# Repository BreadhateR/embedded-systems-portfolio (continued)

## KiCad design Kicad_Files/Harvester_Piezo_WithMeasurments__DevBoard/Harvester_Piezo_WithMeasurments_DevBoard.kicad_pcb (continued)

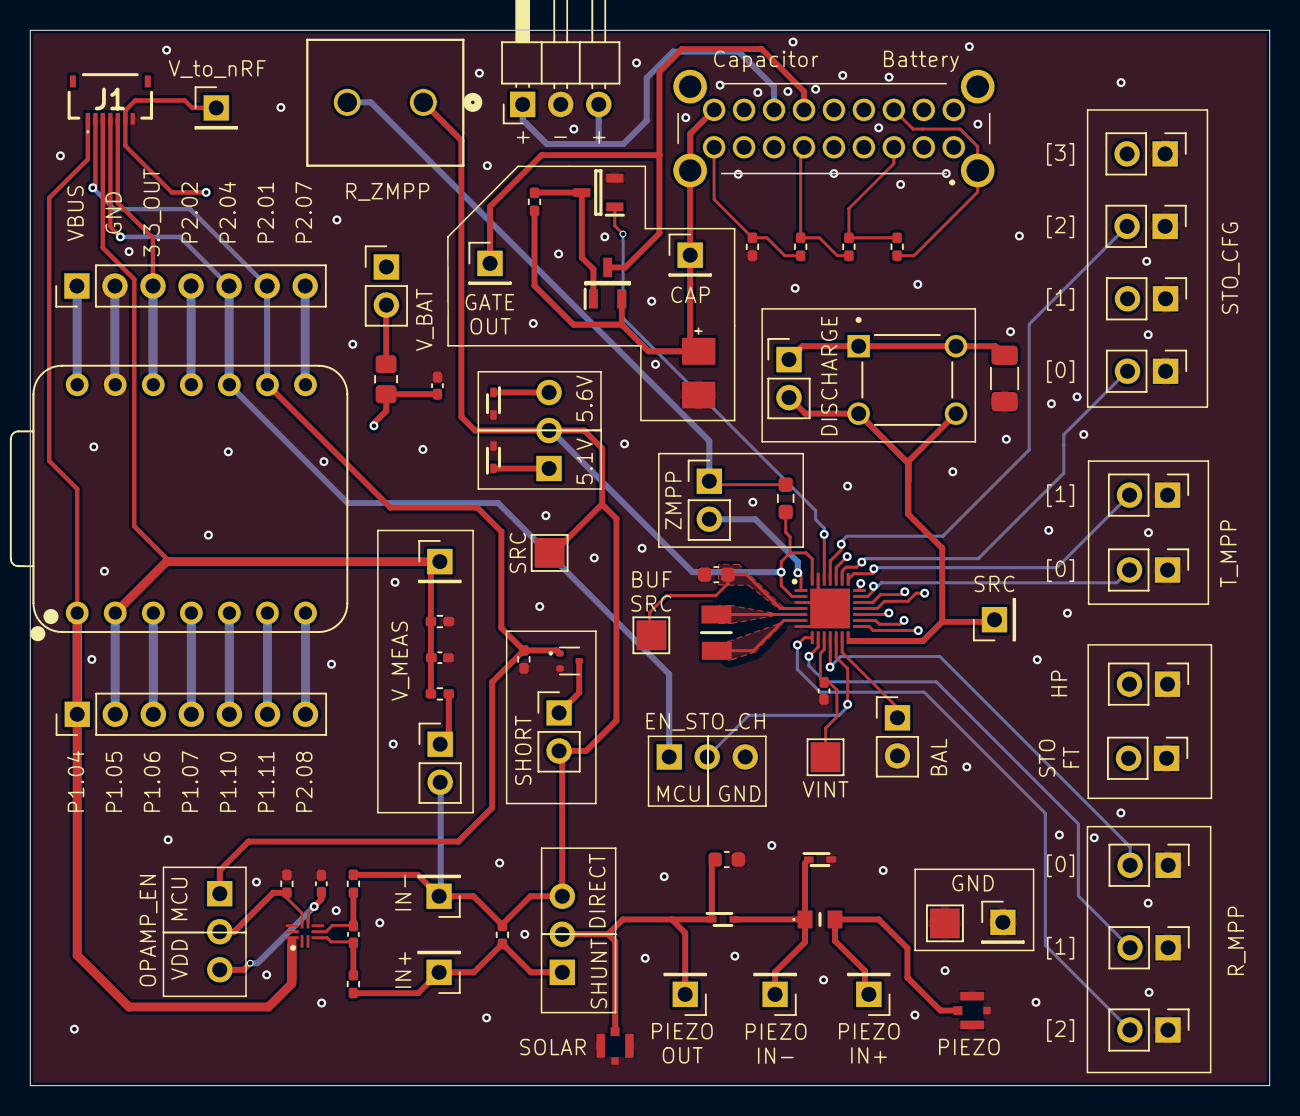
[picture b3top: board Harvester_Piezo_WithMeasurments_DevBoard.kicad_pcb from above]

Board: 4 copper layers, 82.7 x 70.5 mm, 80 parts (0 on the bottom side), 61 nets.

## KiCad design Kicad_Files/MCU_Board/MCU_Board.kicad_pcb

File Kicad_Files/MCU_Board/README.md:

# Nordic nRF54L Custom Development Board

Custom Nordic MCU development-board design for firmware prototyping, peripheral access, and debugging. The supplied schematic and PCB specify **`NRF54L15-QFAA-R`**; 

Development covered the MCU support circuit, supply filtering and decoupling, clock components, RF network, schematic capture, and PCB layout. This is a separate board design; it is not the existing flexible SiSmaK electronics.

## Hardware Features

- **Microcontroller:** Nordic nRF54L15 in the supplied Value/MPN fields
- **RF Circuit:** Discrete matching network and ACAG0201-2450-T chip antenna
- **Clocking:** External high-frequency crystal oscillator
- **Power Supply:** Direct external supply with MCU decoupling and filtering
- **Debugging:** SWD interface for programming and debugging
- **GPIO Expansion:** Pin headers providing access to MCU GPIOs and peripheral interfaces
- **User Interface:** Reset button, user button, and two status LEDs

### Debugging and Peripheral Access

SWDIO, SWDCLK, and reset connections provide programming/debug access. Pin headers expose GPIOs, including signals labelled for peripheral buses, so external circuits can be connected without modifying the PCB.

Two LEDs, a user button, and a reset button provide local controls and status outputs. These are hardware provisions; tested firmware drivers and peripheral functionality are not documented for this board.

## PCB Design

The four-layer PCB was designed using **KiCad 9**. The project includes custom design rules alongside the schematic and layout.

### PCB Layout

## Schematics

The existing hardware PDF export is available here:

[View Schematic (PDF)](Hardware_Design.pdf)

The original KiCad project files are also included for further inspection.

## Design Files

| File | Description |
|---|---|
| [`MCU_Board.kicad_pro`](MCU_Board.kicad_pro) | KiCad project |
| [`MCU_Board.kicad_sch`](MCU_Board.kicad_sch) | Main schematic |
| [`MCU.kicad_sch`](MCU.kicad_sch) | MCU schematic sheet |
| [`MCU_Board.kicad_pcb`](MCU_Board.kicad_pcb) | PCB layout |
| [`MCU_Board.kicad_dru`](MCU_Board.kicad_dru) | Custom design rules |

---

**Author:** Alexander Richter  
**Institution:** TU Darmstadt

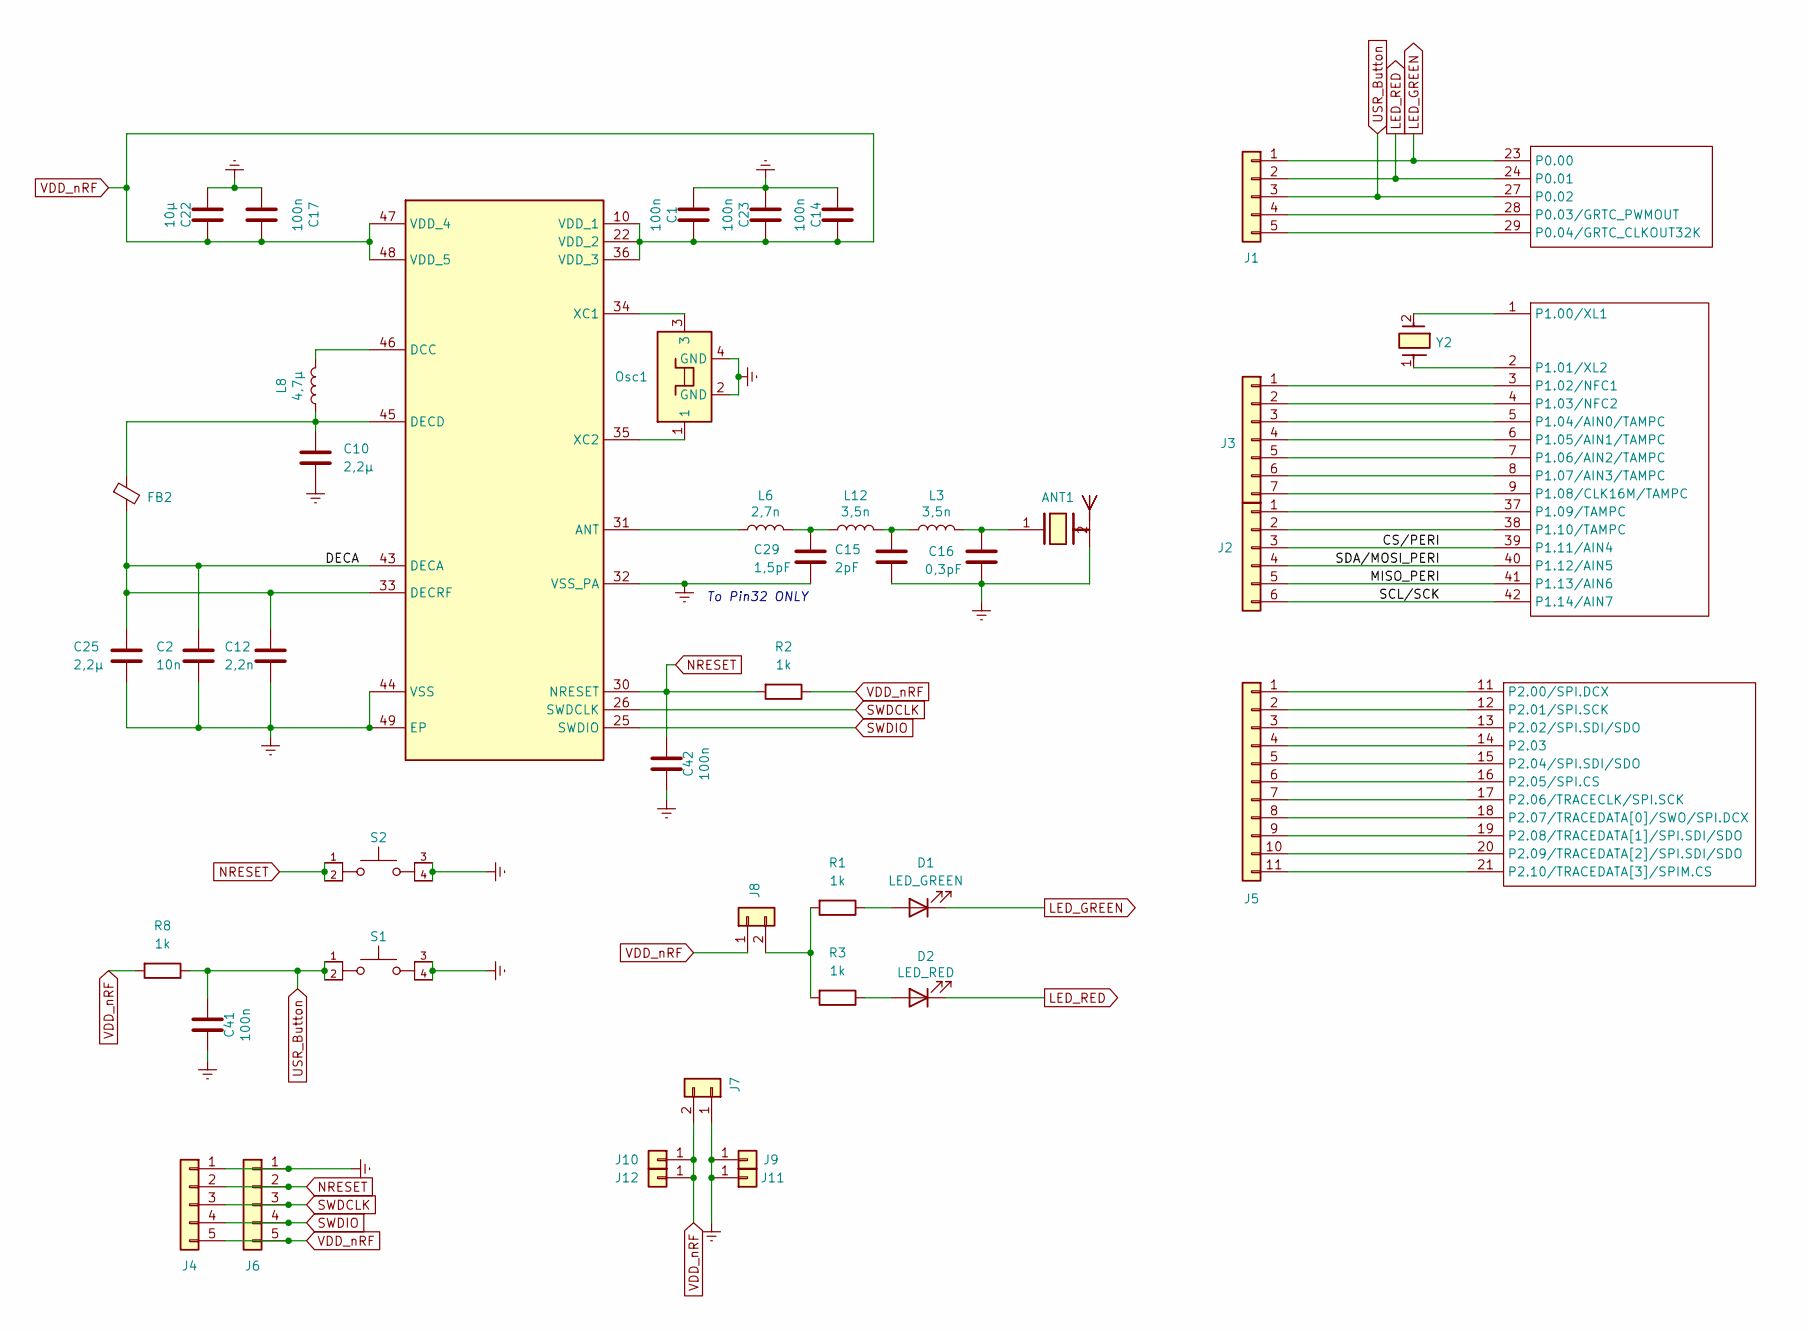
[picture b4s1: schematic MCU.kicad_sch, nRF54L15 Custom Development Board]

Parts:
ANT1: ACAG0201-2450-T; ANTC2012X70N; Manufacturer_Part_Number ACAG0201-2450-T; Mouser Part Number 815-G0201-2450-T
C1, C14, C17, C23, C41, C42: 100n; C_0603_1608Metric_Pad1.08x0.95mm_HandSolder; MPN CC0603KRX7R7BB104
C2: 10n; C_0603_1608Metric_Pad1.08x0.95mm_HandSolder; MPN C0603C103K9RACTU
C10, C25: 2,2µ; C_0603_1608Metric_Pad1.08x0.95mm_HandSolder; MPN CGA3E1X7R0J225K080AC
C12: 2,2n; C_0603_1608Metric_Pad1.08x0.95mm_HandSolder; MPN CC0603KRX7R7BB222
C15: 2pF; C_0603_1608Metric_Pad1.08x0.95mm_HandSolder; MPN RF18N2R0A500CT
C16: 0,3pF; C_0603_1608Metric_Pad1.08x0.95mm_HandSolder; MPN RF18N0R3B500CT
C22: 10µ; C_0603_1608Metric_Pad1.08x0.95mm_HandSolder; MPN CL10A106KQ8NNNC
C29: 1,5pF; C_0603_1608Metric_Pad1.08x0.95mm_HandSolder; MPN RF18N1R5A500CT
D1: LED_GREEN; LED_0603_1608Metric_Pad1.05x0.95mm_HandSolder; MPN APT1608CGCK
D2: LED_RED; LED_0603_1608Metric_Pad1.05x0.95mm_HandSolder; MPN VFHR1111C-3BY2A-TR
FB2: FerriteBead_Small; L_0603_1608Metric_Pad1.05x0.95mm_HandSolder; MPN 2506031217H0
IC1: NRF54L10-QFAA-R; QFN40P600X600X90-49N; Mouser Part Number 949-NRF54L10-QFAA-R
J1, J6: Conn_01x05; PinHeader_1x05_P2.54mm_Vertical
J2: Conn_01x06; PinHeader_1x06_P2.54mm_Vertical
J3: Conn_01x07; PinHeader_1x07_P2.54mm_Vertical
J4: Conn_01x05; JST_XH_B5B-XH-A_1x05_P2.50mm_Vertical
J5: Conn_01x11; PinHeader_1x11_P2.54mm_Vertical
J7: Conn_01x02; TerminalBlock_MetzConnect_Type059_RT06302HBWC_1x02_P3.50mm_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
J8: Conn_01x02; PinHeader_1x02_P2.54mm_Vertical
J9, J10: Conn_01x01; PinHeader_1x01_P2.54mm_Vertical
J11, J12: Conn_01x01; PinHeader_1x01_P2.54mm_Horizontal
L3, L12: 3,5n; L_0402_1005Metric; MPN MHQ1005075HA3N5BTD25
L6: 2,7n; L_0603_1608Metric_Pad1.05x0.95mm_HandSolder; MPN L06032R7BGWTR
L8: 4,7µ; L_0603_1608Metric_Pad1.05x0.95mm_HandSolder; MPN ASMCI-0603-4R7M-T
Osc1: Crystall_main; ECS-320-CDX-2374; MPN ECS-320-CDX-2374
R1, R2, R3, R8: 1k; R_0603_1608Metric_Pad0.98x0.95mm_HandSolder; MPN RMCF0603FT1K00
S1, S2: SWT0315-065025GSA_REVA; SW_SWT0315-065025GSA_REVA; PARTREV A
Y2: SC16S-7PF20PPM; SC16S7PF20PPM; Manufacturer_Part_Number SC16S-7PF20PPM; Mouser Part Number 628-SC16S-7PF20PPM

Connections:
/MCU/CS/PERI: IC1.39 (P1.11/AIN4), J2.3
/MCU/DECA: C2.2, C12.2, C25.2, FB2.2, IC1.33 (DECRF), IC1.43 (DECA)
/MCU/MISO_PERI: IC1.41 (P1.13/AIN6), J2.5
/MCU/SCL/SCK: IC1.42 (P1.14/AIN7), J2.6
/MCU/SDA/MOSI_PERI: IC1.40 (P1.12/AIN5), J2.4
Earth: ANT1.2, C1.2, C2.1, C10.1, C12.1, C14.2, C15.1, C16.1, C17.2, C22.2, C23.2, C25.1, C29.1, C41.2, C42.2, IC1.32 (VSS_PA), IC1.44 (VSS), IC1.49 (EP), J4.1, J6.1, J7.1, J9.1, J11.1, Osc1.2 (GND), Osc1.4 (GND), S1.3, S1.4, S2.3, S2.4
LED_GREEN: D1.1 (K), IC1.23 (P0.00), J1.1
LED_RED: D2.1 (K), IC1.24 (P0.01), J1.2
NRESET: C42.1, IC1.30 (NRESET), J4.2, J6.2, R2.2, S2.1, S2.2
unnamed: ANT1.1, C16.2, L3.2
unnamed: C15.2, L3.1, L12.2
unnamed: C29.2, L6.2, L12.1
unnamed: D1.2 (A), R1.1
unnamed: D2.2 (A), R3.1
unnamed: IC1.31 (ANT), L6.1
unnamed: IC1.46 (DCC), L8.2
unnamed: C10.2, FB2.1, IC1.45 (DECD), L8.1
unnamed: IC1.34 (XC1), Osc1.3
unnamed: IC1.35 (XC2), Osc1.1
unnamed: IC1.28 (P0.03/GRTC_PWMOUT), J1.4
unnamed: IC1.29 (P0.04/GRTC_CLKOUT32K), J1.5
unnamed: IC1.1 (P1.00/XL1), Y2.2 (CRYSTAL_2)
unnamed: IC1.2 (P1.01/XL2), Y2.1
unnamed: IC1.3 (P1.02/NFC1), J3.1
unnamed: IC1.4 (P1.03/NFC2), J3.2
unnamed: IC1.5 (P1.04/AIN0/TAMPC), J3.3
unnamed: IC1.6 (P1.05/AIN1/TAMPC), J3.4
unnamed: IC1.7 (P1.06/AIN2/TAMPC), J3.5
unnamed: IC1.8 (P1.07/AIN3/TAMPC), J3.6
unnamed: IC1.9 (P1.08/CLK16M/TAMPC), J3.7
unnamed: IC1.37 (P1.09/TAMPC), J2.1
unnamed: IC1.38 (P1.10/TAMPC), J2.2
unnamed: IC1.11 (P2.00/SPI.DCX), J5.1
unnamed: IC1.12 (P2.01/SPI.SCK), J5.2
unnamed: IC1.13 (P2.02/SPI.SDI/SDO), J5.3
unnamed: IC1.14 (P2.03), J5.4
unnamed: IC1.15 (P2.04/SPI.SDI/SDO), J5.5
unnamed: IC1.16 (P2.05/SPI.CS), J5.6
unnamed: IC1.17 (P2.06/TRACECLK/SPI.SCK), J5.7
unnamed: IC1.18 (P2.07/TRACEDATA[0]/SWO/SPI.DCX), J5.8
unnamed: IC1.19 (P2.08/TRACEDATA[1]/SPI.SDI/SDO), J5.9
unnamed: IC1.20 (P2.09/TRACEDATA[2]/SPI.SDI/SDO), J5.10
unnamed: IC1.21 (P2.10/TRACEDATA[3]/SPIM.CS), J5.11
unnamed: J8.2, R1.2, R3.2
SWDCLK: IC1.26 (SWDCLK), J4.3, J6.3
SWDIO: IC1.25 (SWDIO), J4.4, J6.4
USR_Button: C41.1, IC1.27 (P0.02), J1.3, R8.1, S1.1, S1.2
VDD_nRF: C1.1, C14.1, C17.1, C22.1, C23.1, IC1.10 (VDD_1), IC1.22 (VDD_2), IC1.36 (VDD_3), IC1.47 (VDD_4), IC1.48 (VDD_5), J4.5, J6.5, J7.2, J8.1, J10.1, J12.1, R2.1, R8.2

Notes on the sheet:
To Pin32 ONLY

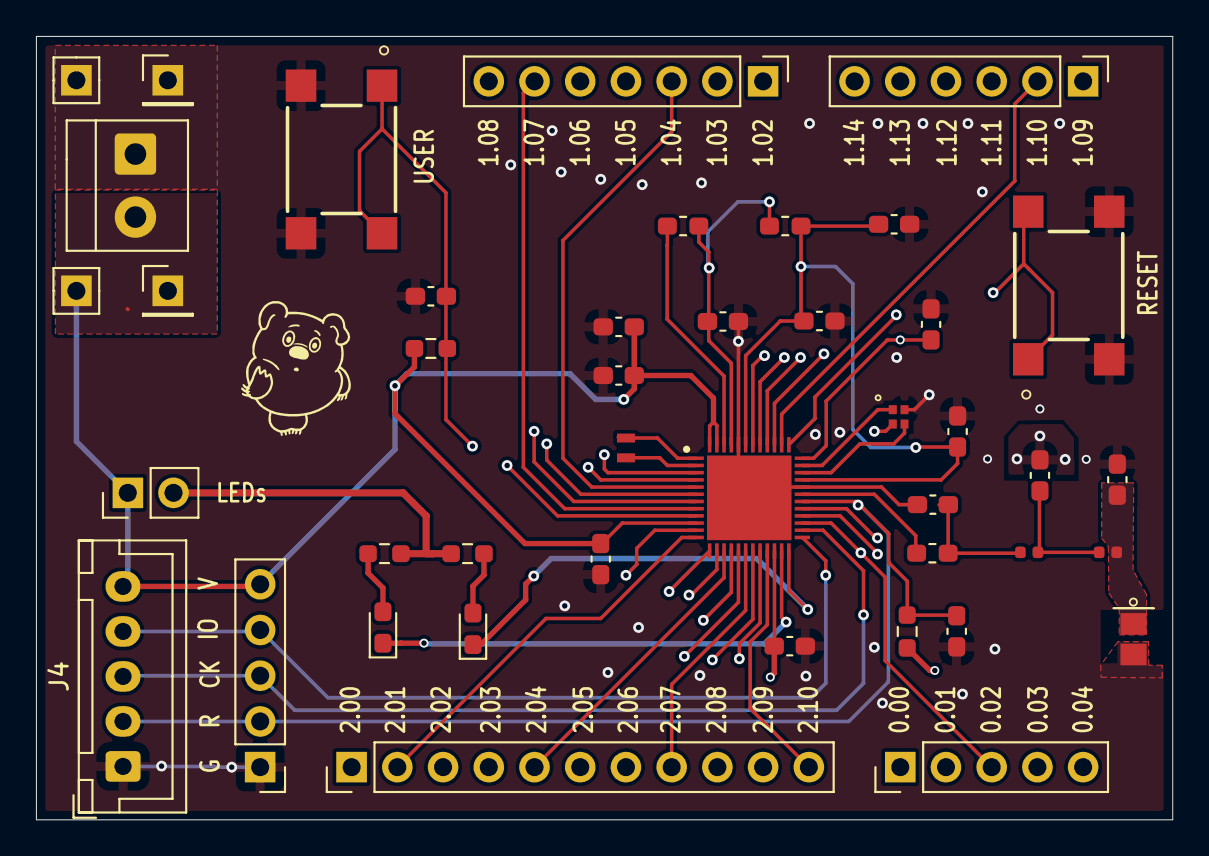
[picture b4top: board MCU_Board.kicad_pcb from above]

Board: 4 copper layers, 63.1 x 43.5 mm, 43 parts (0 on the bottom side), 48 nets.

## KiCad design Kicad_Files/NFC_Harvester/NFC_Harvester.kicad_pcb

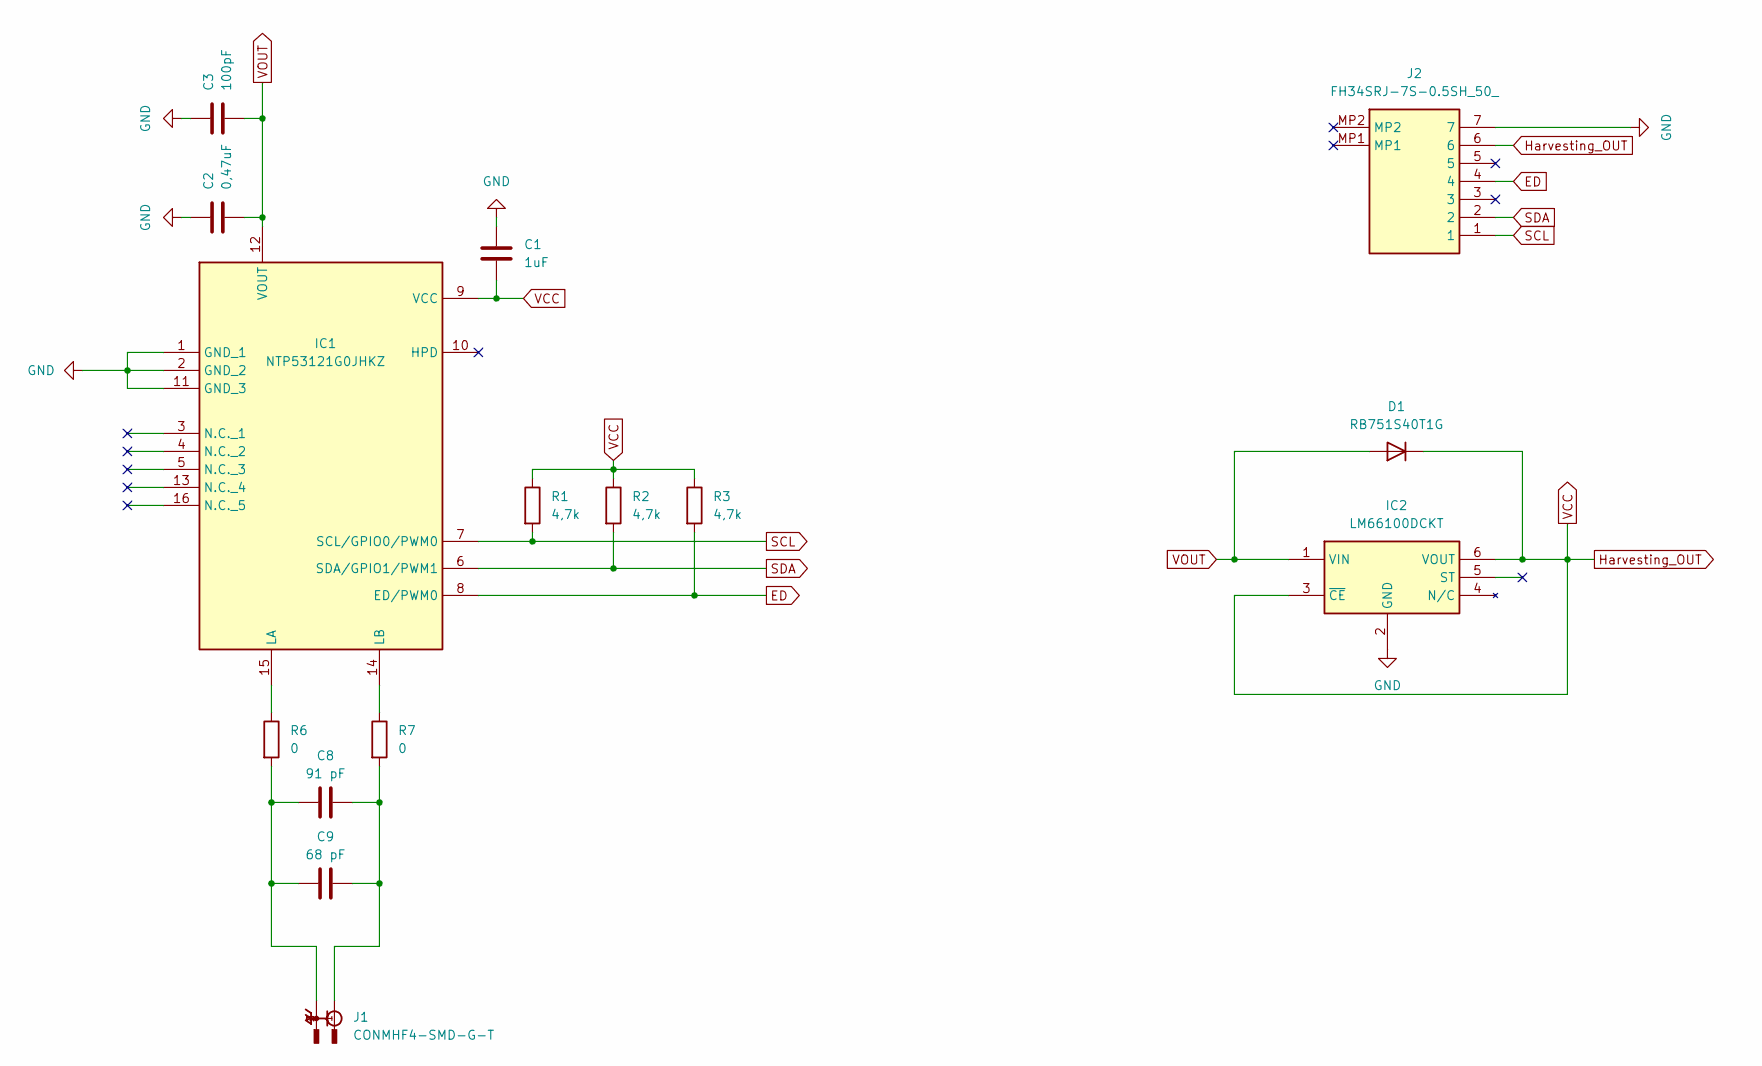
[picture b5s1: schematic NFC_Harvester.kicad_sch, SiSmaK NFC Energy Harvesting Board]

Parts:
C1: 1uF; C_0402_1005Metric_Pad0.74x0.62mm_HandSolder; MPN GRM155R61E105MA12D
C2: 0,47uF; C_0402_1005Metric_Pad0.74x0.62mm_HandSolder; MPN MSASE105AB5474MFNA01
C3: 100pF; C_0402_1005Metric_Pad0.74x0.62mm_HandSolder; MPN CC0402KRX7R7BB101
C8: 91 pF; C_0402_1005Metric_Pad0.74x0.62mm_HandSolder; MPN GCM1555C1H910FA16D
C9: 68 pF; C_0402_1005Metric_Pad0.74x0.62mm_HandSolder; MPN GCM1555C1H680FA16J
D1: RB751S40T1G; Diode_RB751S40T1G; MPN RB751S40T1G
IC1: NTP53121G0JHKZ; Manufacturer_Part_Number NTP53121G0JHKZ; Mouser Part Number 771-NTP53121G0JHKZ
IC2: LM66100DCKT; Manufacturer_Part_Number LM66100DCKT; Mouser Part Number 595-LM66100DCKT
J1: CONMHF4-SMD-G-T; PARTREV A
J2: FH34SRJ-7S-0.5SH_50_; FH34SRJ7S05SH50; Manufacturer_Part_Number FH34SRJ-7S-0.5SH(50); Mouser Part Number 798-FH34SRJ7S05SH50
R1, R2, R3: 4,7k; R_0402_1005Metric_Pad0.72x0.64mm_HandSolder; MPN RCG04024K70JNED
R6, R7: 0; R_0402_1005Metric_Pad0.72x0.64mm_HandSolder; MPN RCS04020000Z0ED

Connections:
ED: IC1.8 (ED/PWM0), J2.4, R3.2
GND: C1.1, C2.1, C3.1, IC1.1 (GND_1), IC1.2 (GND_2), IC1.11 (GND_3), IC2.2 (GND), J2.7
Harvesting_OUT: C1.2, D1.1 (K), IC1.9 (VCC), IC2.3 (~CE), IC2.6 (VOUT), J2.6, R1.1, R2.1, R3.1
unnamed: C8.1, C9.1, J1.2, J1.3, J1.4, R6.2
unnamed: C8.2, C9.2, J1.1, R7.2
unnamed: IC1.15 (LA), R6.1
unnamed: IC1.14 (LB), R7.1
SCL: IC1.7 (SCL/GPIO0/PWM0), J2.1, R1.2
SDA: IC1.6 (SDA/GPIO1/PWM1), J2.2, R2.2
VOUT: C2.2, C3.2, D1.2 (A), IC1.12 (VOUT), IC2.1 (VIN)

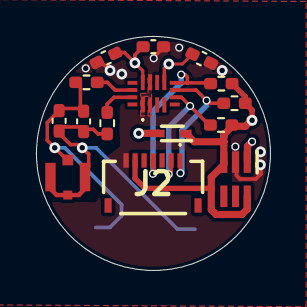
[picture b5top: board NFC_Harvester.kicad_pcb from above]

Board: 4 copper layers, 13.0 x 13.0 mm, 15 parts (0 on the bottom side), 10 nets.
